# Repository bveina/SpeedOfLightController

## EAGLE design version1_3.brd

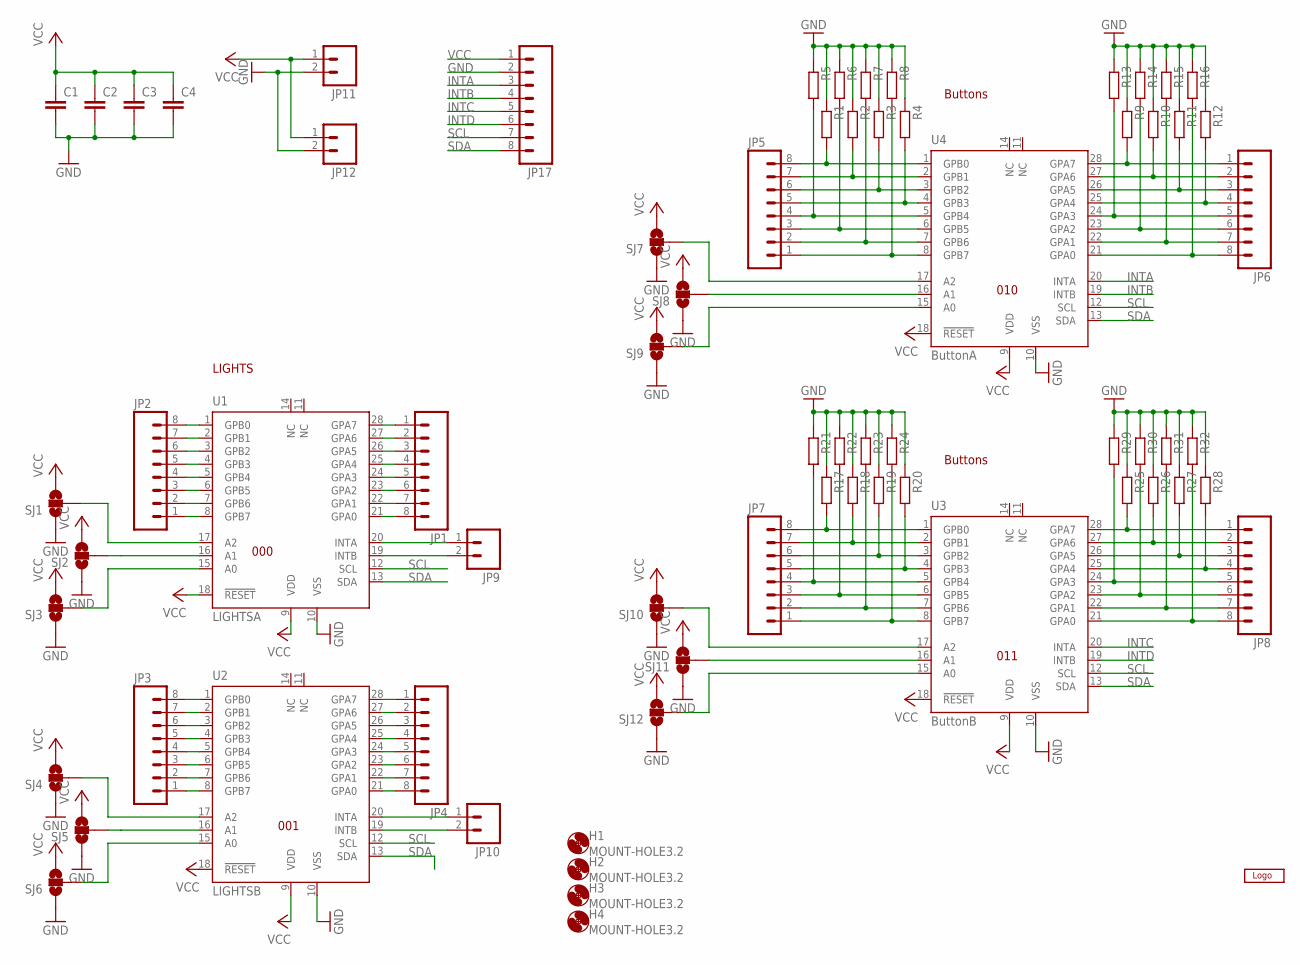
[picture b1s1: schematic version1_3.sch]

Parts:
C1, C2, C3, C4: C-EUC0805; C0805
H1, H2, H3, H4: MOUNT-HOLE3.2; 3,2
JP1, JP2, JP3, JP4, JP5, JP6, JP7, JP8, JP17: M08LOCK; 1X08_LOCK
JP9, JP10, JP11, JP12: M021X02_NO_SILK; 1X02_NO_SILK
R1, R2, R3, R4, R5, R6, R7, R8, R9, R10, R11, R12, R13, R14, R15, R16, R17, R18, R19, R20, R21, R22, R23, R24, R25, R26, R27, R28, R29, R30, R31, R32: R-EU_R0805; R0805
SJ1, SJ2, SJ3, SJ4, SJ5, SJ6, SJ7, SJ8, SJ9, SJ10, SJ11, SJ12: SOLDERJUMPER_2WAY-OLDS; SJ_3
U1: LIGHTSA; MCP23017A
U2: LIGHTSB; MCP23017A
U3: ButtonB; MCP23017A
U4: ButtonA; MCP23017A
U$1: BUNNYLOGOCALVIN2; CALVIN2

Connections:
GND: C1.2, C2.2, C3.2, C4.2, JP11.2, JP12.2, JP17.2, R1.1, R2.1, R3.1, R4.1, R5.1, R6.1, R7.1, R8.1, R9.1, R10.1, R11.1, R12.1, R13.1, R14.1, R15.1, R16.1, R17.1, R18.1, R19.1, R20.1, R21.1, R22.1, R23.1, R24.1, R25.1, R26.1, R27.1, R28.1, R29.1, R30.1, R31.1, R32.1, SJ1.1, SJ2.1, SJ3.1, SJ4.1, SJ5.1, SJ6.1, SJ7.1, SJ8.1, SJ9.1, SJ10.1, SJ11.1, SJ12.1, U1.10 (VSS), U2.10 (VSS), U3.10 (VSS), U4.10 (VSS)
INTA: JP17.3, U4.20 (INTA)
INTB: JP17.4, U4.19 (INTB)
INTC: JP17.5, U3.20 (INTA)
INTD: JP17.6, U3.19 (INTB)
unnamed: JP1.1, U1.28 (GPA7)
unnamed: JP1.2, U1.27 (GPA6)
unnamed: JP1.3, U1.26 (GPA5)
unnamed: JP1.4, U1.25 (GPA4)
unnamed: JP1.5, U1.24 (GPA3)
unnamed: JP1.6, U1.23 (GPA2)
unnamed: JP1.7, U1.22 (GPA1)
unnamed: JP1.8, U1.21 (GPA0)
unnamed: JP2.1, U1.8 (GPB7)
unnamed: JP2.2, U1.7 (GPB6)
unnamed: JP2.3, U1.6 (GPB5)
unnamed: JP2.4, U1.5 (GPB4)
unnamed: JP2.5, U1.4 (GPB3)
unnamed: JP2.6, U1.3 (GPB2)
unnamed: JP2.7, U1.2 (GPB1)
unnamed: JP2.8, U1.1 (GPB0)
unnamed: JP3.1, U2.8 (GPB7)
unnamed: JP3.2, U2.7 (GPB6)
unnamed: JP3.3, U2.6 (GPB5)
unnamed: JP3.4, U2.5 (GPB4)
unnamed: JP3.5, U2.4 (GPB3)
unnamed: JP3.6, U2.3 (GPB2)
unnamed: JP3.7, U2.2 (GPB1)
unnamed: JP3.8, U2.1 (GPB0)
unnamed: JP4.1, U2.28 (GPA7)
unnamed: JP4.2, U2.27 (GPA6)
unnamed: JP4.3, U2.26 (GPA5)
unnamed: JP4.4, U2.25 (GPA4)
unnamed: JP4.5, U2.24 (GPA3)
unnamed: JP4.6, U2.23 (GPA2)
unnamed: JP4.7, U2.22 (GPA1)
unnamed: JP4.8, U2.21 (GPA0)
unnamed: JP5.1, R8.2, U4.8 (GPB7)
unnamed: JP5.2, R7.2, U4.7 (GPB6)
unnamed: JP5.3, R6.2, U4.6 (GPB5)
unnamed: JP5.4, R5.2, U4.5 (GPB4)
unnamed: JP5.5, R4.2, U4.4 (GPB3)
unnamed: JP5.6, R3.2, U4.3 (GPB2)
unnamed: JP5.7, R2.2, U4.2 (GPB1)
unnamed: JP5.8, R1.2, U4.1 (GPB0)
unnamed: JP6.1, R9.2, U4.28 (GPA7)
unnamed: JP6.2, R10.2, U4.27 (GPA6)
unnamed: JP6.3, R11.2, U4.26 (GPA5)
unnamed: JP6.4, R12.2, U4.25 (GPA4)
unnamed: JP6.5, R13.2, U4.24 (GPA3)
unnamed: JP6.6, R14.2, U4.23 (GPA2)
unnamed: JP6.7, R15.2, U4.22 (GPA1)
unnamed: JP6.8, R16.2, U4.21 (GPA0)
unnamed: JP7.1, R24.2, U3.8 (GPB7)
unnamed: JP7.2, R23.2, U3.7 (GPB6)
unnamed: JP7.3, R22.2, U3.6 (GPB5)
unnamed: JP7.4, R21.2, U3.5 (GPB4)
unnamed: JP7.5, R20.2, U3.4 (GPB3)
unnamed: JP7.6, R19.2, U3.3 (GPB2)
unnamed: JP7.7, R18.2, U3.2 (GPB1)
unnamed: JP7.8, R17.2, U3.1 (GPB0)
unnamed: JP8.1, R25.2, U3.28 (GPA7)
unnamed: JP8.2, R26.2, U3.27 (GPA6)
unnamed: JP8.3, R27.2, U3.26 (GPA5)
unnamed: JP8.4, R28.2, U3.25 (GPA4)
unnamed: JP8.5, R29.2, U3.24 (GPA3)
unnamed: JP8.6, R30.2, U3.23 (GPA2)
unnamed: JP8.7, R31.2, U3.22 (GPA1)
unnamed: JP8.8, R32.2, U3.21 (GPA0)
unnamed: JP10.1, U2.20 (INTA)
unnamed: JP10.2, U2.19 (INTB)
unnamed: JP9.1, U1.20 (INTA)
unnamed: JP9.2, U1.19 (INTB)
unnamed: SJ4.2, U2.17 (A2)
unnamed: SJ5.2, U2.16 (A1)
unnamed: SJ6.2, U2.15 (A0)
unnamed: SJ10.2, U3.17 (A2)
unnamed: SJ11.2, U3.16 (A1)
unnamed: SJ12.2, U3.15 (A0)
unnamed: SJ2.2, U1.16 (A1)
unnamed: SJ3.2, U1.15 (A0)
unnamed: SJ1.2, U1.17 (A2)
unnamed: SJ7.2, U4.17 (A2)
unnamed: SJ8.2, U4.16 (A1)
unnamed: SJ9.2, U4.15 (A0)
SCL: JP17.7, U1.12 (SCL), U2.12 (SCL), U3.12 (SCL), U4.12 (SCL)
SDA: JP17.8, U1.13 (SDA), U2.13 (SDA), U3.13 (SDA), U4.13 (SDA)
VCC: C1.1, C2.1, C3.1, C4.1, JP11.1, JP12.1, JP17.1, SJ1.3, SJ2.3, SJ3.3, SJ4.3, SJ5.3, SJ6.3, SJ7.3, SJ8.3, SJ9.3, SJ10.3, SJ11.3, SJ12.3, U1.9 (VDD), U1.18 (!RESET), U2.9 (VDD), U2.18 (!RESET), U3.9 (VDD), U3.18 (!RESET), U4.9 (VDD), U4.18 (!RESET)

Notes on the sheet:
LIGHTS
Buttons
000
010
011
001

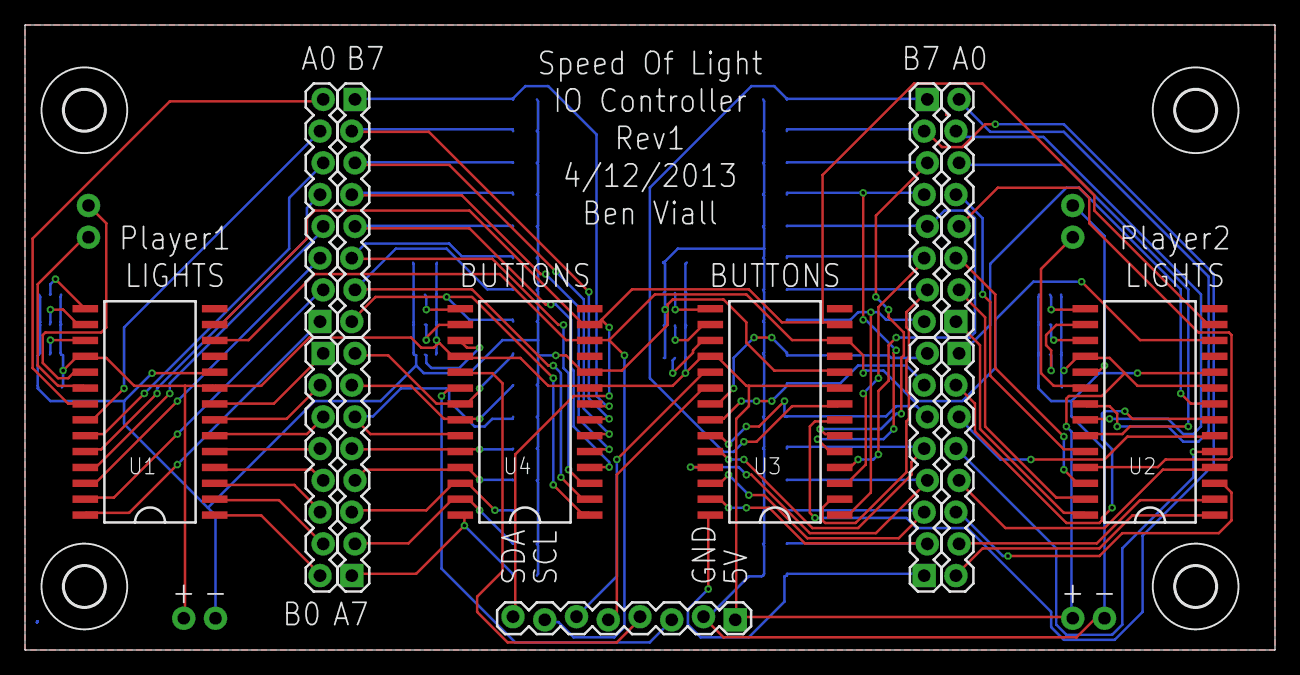
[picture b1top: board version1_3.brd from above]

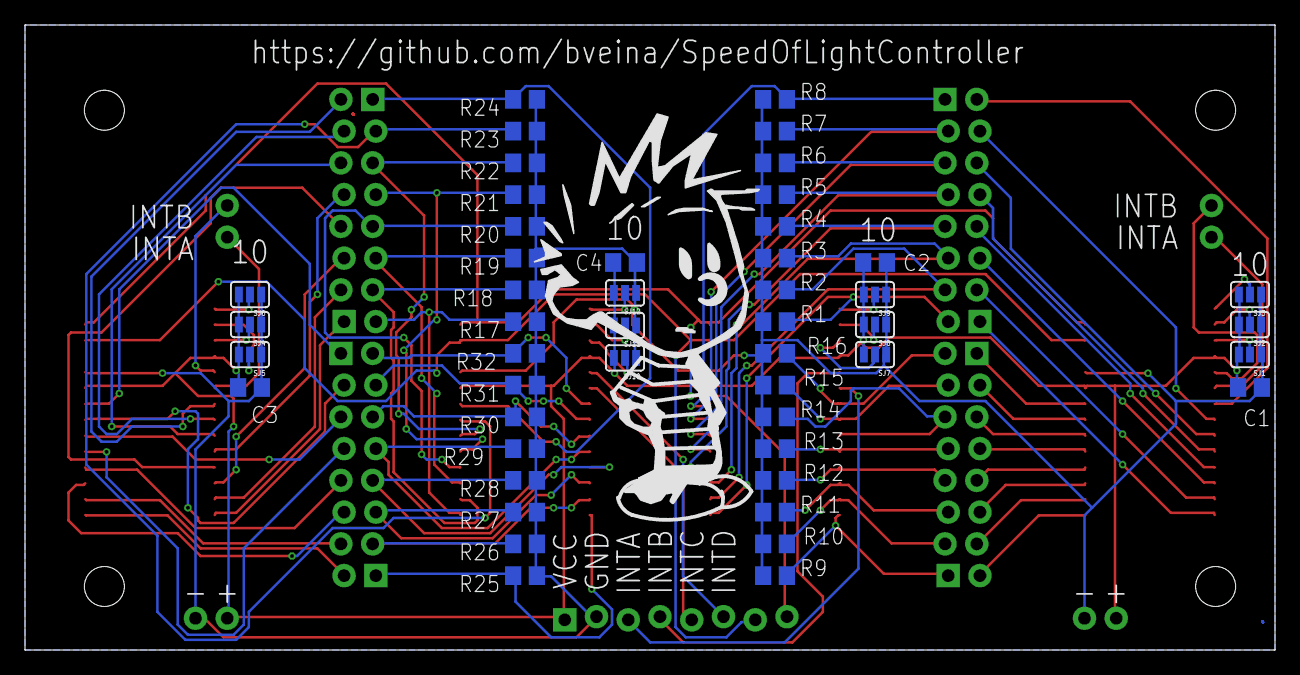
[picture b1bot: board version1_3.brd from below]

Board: 2 copper layers, 100.0 x 50.0 mm, 70 parts (49 on the bottom side), 88 nets.

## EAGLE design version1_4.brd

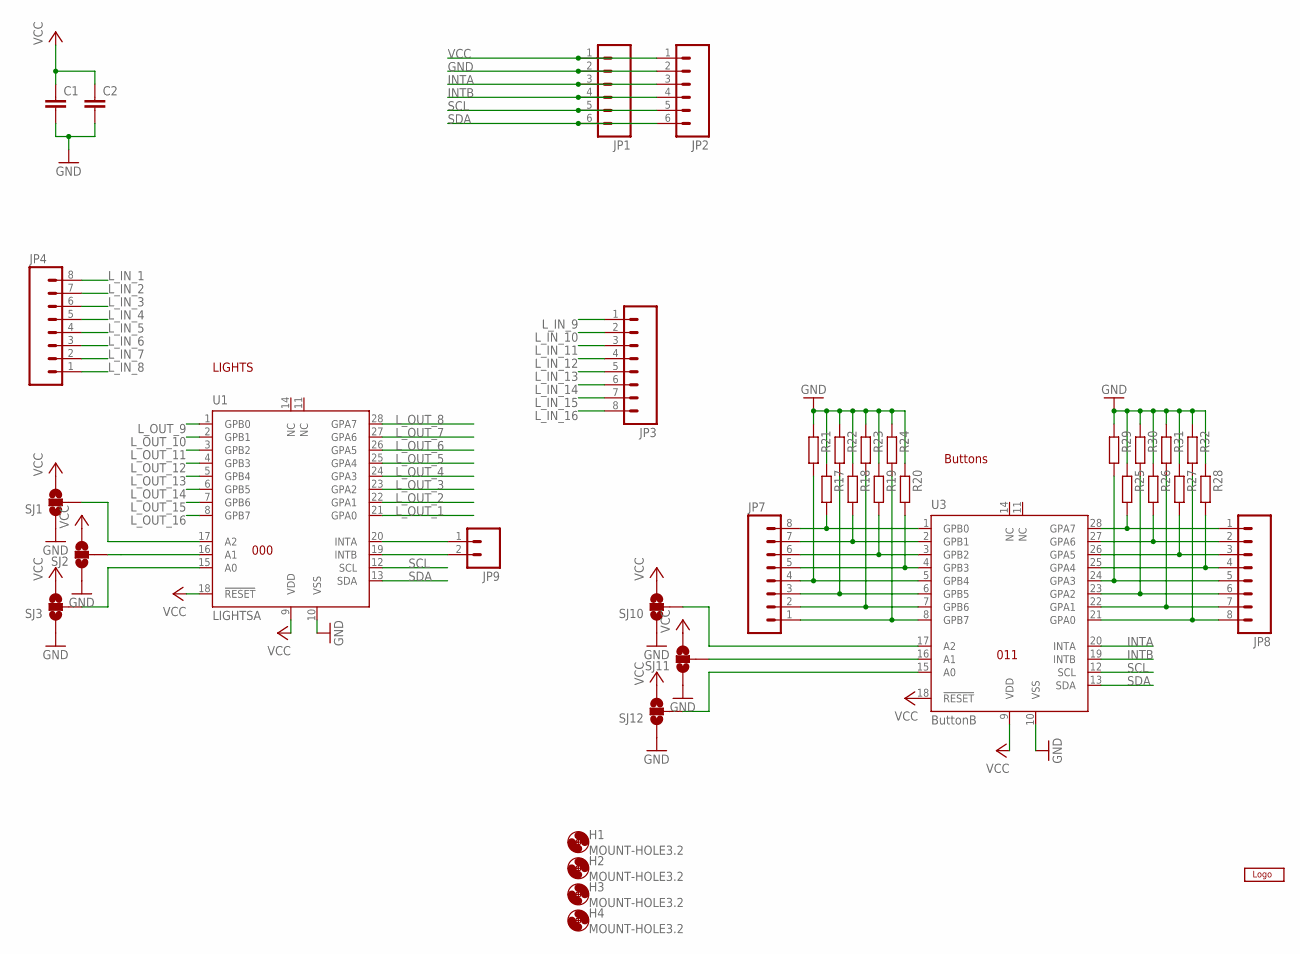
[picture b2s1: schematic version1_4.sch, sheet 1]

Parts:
C1, C2: C-EUC0805; C0805
H1, H2, H3, H4: MOUNT-HOLE3.2; 3,2
JP1, JP2: M06LOCK; 1X06_LOCK
JP3, JP4, JP7, JP8: M08LOCK; 1X08_LOCK
JP9: M021X02_NO_SILK; 1X02_NO_SILK
R17, R18, R19, R20, R21, R22, R23, R24, R25, R26, R27, R28, R29, R30, R31, R32: R-EU_R0805; R0805
SJ1, SJ2, SJ3, SJ10, SJ11, SJ12: SOLDERJUMPER_2WAY-OLDS; SJ_3
U1: LIGHTSA; MCP23017A
U3: ButtonB; MCP23017A
U$1: BUNNYLOGOCALVIN2; CALVIN2

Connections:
GND: C1.2, C2.2, JP1.2, JP2.2, R17.1, R18.1, R19.1, R20.1, R21.1, R22.1, R23.1, R24.1, R25.1, R26.1, R27.1, R28.1, R29.1, R30.1, R31.1, R32.1, SJ1.1, SJ2.1, SJ3.1, SJ10.1, SJ11.1, SJ12.1, U1.10 (VSS), U3.10 (VSS); also elsewhere on the board
INTA: JP1.3, JP2.3, U3.20 (INTA)
INTB: JP1.4, JP2.4, U3.19 (INTB)
L_IN_1: JP4.8; also elsewhere on the board
L_IN_2: JP4.7; also elsewhere on the board
L_IN_3: JP4.6; also elsewhere on the board
L_IN_4: JP4.5; also elsewhere on the board
L_IN_5: JP4.4; also elsewhere on the board
L_IN_6: JP4.3; also elsewhere on the board
L_IN_7: JP4.2; also elsewhere on the board
L_IN_8: JP4.1; also elsewhere on the board
L_IN_9: JP3.1; also elsewhere on the board
L_IN_10: JP3.2; also elsewhere on the board
L_IN_11: JP3.3; also elsewhere on the board
L_IN_12: JP3.4; also elsewhere on the board
L_IN_13: JP3.5; also elsewhere on the board
L_IN_14: JP3.6; also elsewhere on the board
L_IN_15: JP3.7; also elsewhere on the board
L_IN_16: JP3.8; also elsewhere on the board
L_OUT_1: U1.21 (GPA0); also elsewhere on the board
L_OUT_2: U1.22 (GPA1); also elsewhere on the board
L_OUT_3: U1.23 (GPA2); also elsewhere on the board
L_OUT_4: U1.24 (GPA3); also elsewhere on the board
L_OUT_5: U1.25 (GPA4); also elsewhere on the board
L_OUT_6: U1.26 (GPA5); also elsewhere on the board
L_OUT_7: U1.27 (GPA6); also elsewhere on the board
L_OUT_8: U1.28 (GPA7); also elsewhere on the board
L_OUT_9: U1.1 (GPB0); also elsewhere on the board
L_OUT_10: U1.2 (GPB1); also elsewhere on the board
L_OUT_11: U1.3 (GPB2); also elsewhere on the board
L_OUT_12: U1.4 (GPB3); also elsewhere on the board
L_OUT_13: U1.5 (GPB4); also elsewhere on the board
L_OUT_14: U1.6 (GPB5); also elsewhere on the board
L_OUT_15: U1.7 (GPB6); also elsewhere on the board
L_OUT_16: U1.8 (GPB7); also elsewhere on the board
unnamed: JP7.1, R24.2, U3.8 (GPB7)
unnamed: JP7.2, R23.2, U3.7 (GPB6)
unnamed: JP7.3, R22.2, U3.6 (GPB5)
unnamed: JP7.4, R21.2, U3.5 (GPB4)
unnamed: JP7.5, R20.2, U3.4 (GPB3)
unnamed: JP7.6, R19.2, U3.3 (GPB2)
unnamed: JP7.7, R18.2, U3.2 (GPB1)
unnamed: JP7.8, R17.2, U3.1 (GPB0)
unnamed: JP8.1, R25.2, U3.28 (GPA7)
unnamed: JP8.2, R26.2, U3.27 (GPA6)
unnamed: JP8.3, R27.2, U3.26 (GPA5)
unnamed: JP8.4, R28.2, U3.25 (GPA4)
unnamed: JP8.5, R29.2, U3.24 (GPA3)
unnamed: JP8.6, R30.2, U3.23 (GPA2)
unnamed: JP8.7, R31.2, U3.22 (GPA1)
unnamed: JP8.8, R32.2, U3.21 (GPA0)
unnamed: JP9.1, U1.20 (INTA)
unnamed: JP9.2, U1.19 (INTB)
unnamed: SJ10.2, U3.17 (A2)
unnamed: SJ11.2, U3.16 (A1)
unnamed: SJ12.2, U3.15 (A0)
unnamed: SJ2.2, U1.16 (A1)
unnamed: SJ3.2, U1.15 (A0)
unnamed: SJ1.2, U1.17 (A2)
SCL: JP1.5, JP2.5, U1.12 (SCL), U3.12 (SCL)
SDA: JP1.6, JP2.6, U1.13 (SDA), U3.13 (SDA)
VCC: C1.1, C2.1, JP1.1, JP2.1, SJ1.3, SJ2.3, SJ3.3, SJ10.3, SJ11.3, SJ12.3, U1.9 (VDD), U1.18 (!RESET), U3.9 (VDD), U3.18 (!RESET)

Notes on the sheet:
LIGHTS
Buttons
000
011

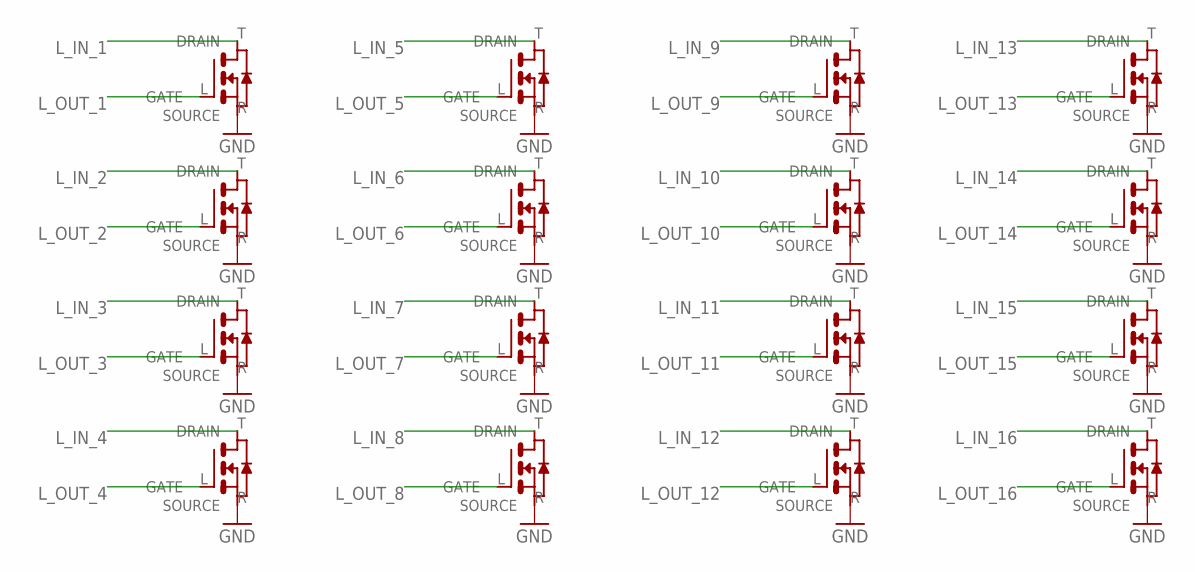
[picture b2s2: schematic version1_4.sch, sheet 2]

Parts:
Q1, Q2, Q3, Q4, Q5, Q6, Q7, Q8, Q9, Q10, Q11, Q12, Q13, Q14, Q15, Q16: DMG2302U; SOT23-3A

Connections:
GND: Q1.R (SOURCE), Q2.R (SOURCE), Q3.R (SOURCE), Q4.R (SOURCE), Q5.R (SOURCE), Q6.R (SOURCE), Q7.R (SOURCE), Q8.R (SOURCE), Q9.R (SOURCE), Q10.R (SOURCE), Q11.R (SOURCE), Q12.R (SOURCE), Q13.R (SOURCE), Q14.R (SOURCE), Q15.R (SOURCE), Q16.R (SOURCE); also elsewhere on the board
L_IN_1: Q2.T (DRAIN); also elsewhere on the board
L_IN_2: Q1.T (DRAIN); also elsewhere on the board
L_IN_3: Q3.T (DRAIN); also elsewhere on the board
L_IN_4: Q4.T (DRAIN); also elsewhere on the board
L_IN_5: Q5.T (DRAIN); also elsewhere on the board
L_IN_6: Q6.T (DRAIN); also elsewhere on the board
L_IN_7: Q7.T (DRAIN); also elsewhere on the board
L_IN_8: Q8.T (DRAIN); also elsewhere on the board
L_IN_9: Q9.T (DRAIN); also elsewhere on the board
L_IN_10: Q10.T (DRAIN); also elsewhere on the board
L_IN_11: Q11.T (DRAIN); also elsewhere on the board
L_IN_12: Q12.T (DRAIN); also elsewhere on the board
L_IN_13: Q13.T (DRAIN); also elsewhere on the board
L_IN_14: Q14.T (DRAIN); also elsewhere on the board
L_IN_15: Q15.T (DRAIN); also elsewhere on the board
L_IN_16: Q16.T (DRAIN); also elsewhere on the board
L_OUT_1: Q2.L (GATE); also elsewhere on the board
L_OUT_2: Q1.L (GATE); also elsewhere on the board
L_OUT_3: Q3.L (GATE); also elsewhere on the board
L_OUT_4: Q4.L (GATE); also elsewhere on the board
L_OUT_5: Q5.L (GATE); also elsewhere on the board
L_OUT_6: Q6.L (GATE); also elsewhere on the board
L_OUT_7: Q7.L (GATE); also elsewhere on the board
L_OUT_8: Q8.L (GATE); also elsewhere on the board
L_OUT_9: Q9.L (GATE); also elsewhere on the board
L_OUT_10: Q10.L (GATE); also elsewhere on the board
L_OUT_11: Q11.L (GATE); also elsewhere on the board
L_OUT_12: Q12.L (GATE); also elsewhere on the board
L_OUT_13: Q13.L (GATE); also elsewhere on the board
L_OUT_14: Q14.L (GATE); also elsewhere on the board
L_OUT_15: Q15.L (GATE); also elsewhere on the board
L_OUT_16: Q16.L (GATE); also elsewhere on the board

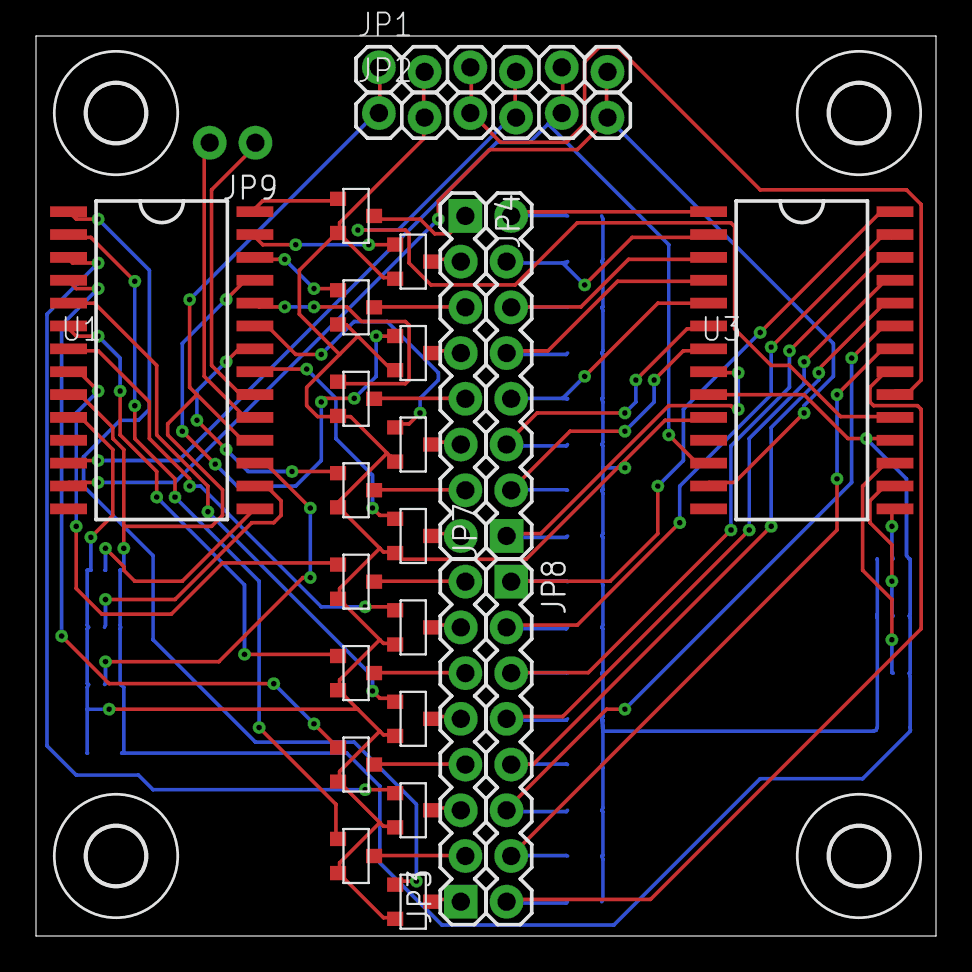
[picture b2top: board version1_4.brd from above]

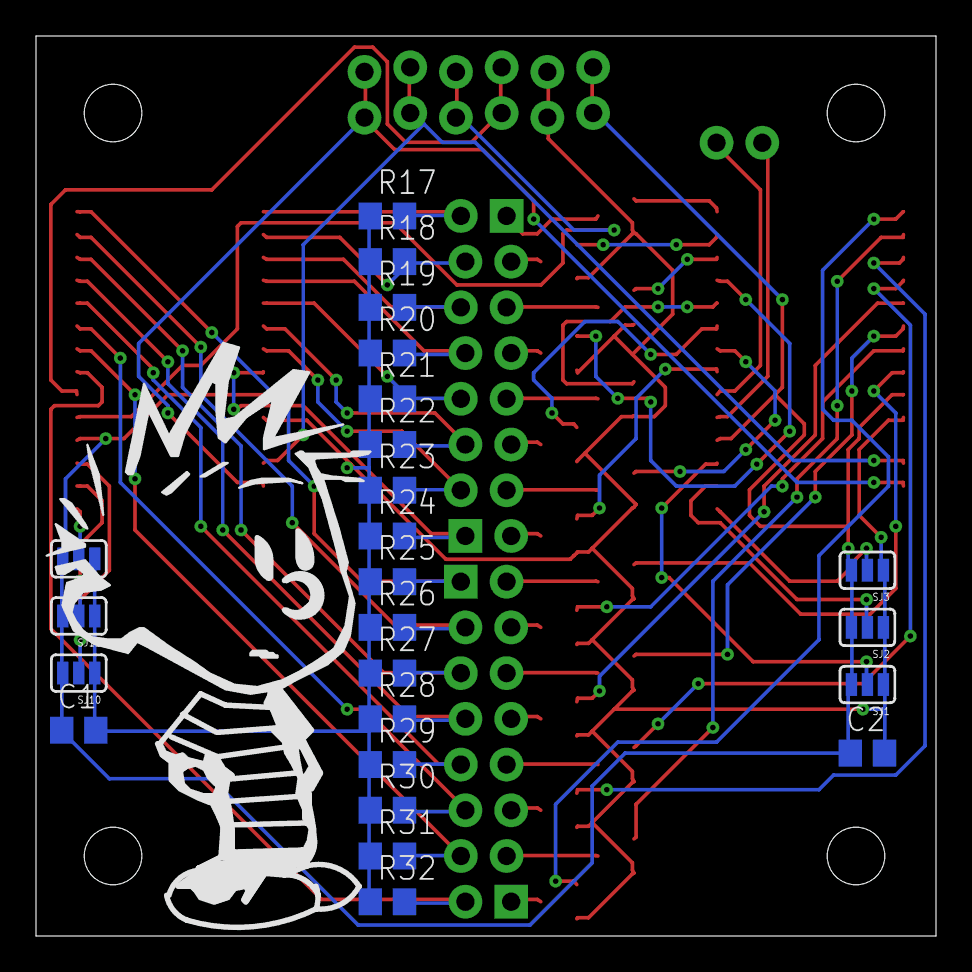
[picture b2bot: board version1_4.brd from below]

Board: 2 copper layers, 50.0 x 50.0 mm, 54 parts (25 on the bottom side), 62 nets.

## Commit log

2013-04-22 Revision 1.3 sent out for fabrication
2016-10-20 folder cleanup and added pdfs and pngs of schematic and layout
2018-11-06 version1_3 pdfs
2018-11-06 add eagle backup files to the git ignore

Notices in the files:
parts and their libraries:
SparkFun: Licensing: CC v3.0 Share-Alike You are welcome to use this library for commercial purposes.
